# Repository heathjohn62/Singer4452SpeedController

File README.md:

# Singer4452-speed-controller

This project implements PID feedback to improve control over the Singer 4452 sewing machine. The modifications are non-destructive to the sewing machine. 

Implement this at your own risk. I do not have an electrical engineering degree nor am I a certified electrician. 120V AC flows through the sewing machine pedal and the PID regulator board, which can electrocute you, start fires, and break things. Don't perform work on circuits that are plugged into the wall. 

As an outline:
1. A rotary encoder tracks the position of the sewing needle by mounting externally to the knob on the side of the machine. The FreeCAD design for the rotary encoder is contained in "rotary-encoder-CAD". Some hardware, a magnet, rubber tape, duct tape, and a ball bearing are also required to assemble this. The PCB for the rotary encoder IC in contained in "speed-sensor-PCB."
2. A network of optoisolated resistors emulate the potentiometer in the existing pedal. Resistance is programmed by a MCU. The MCU and resistor network are enclosed in a chasis, and the design for the PCB is in the folder "Regulator-PCB." The STM32 was programmed in the STM32CubeIDE using the files in the folder "sewing-PID-STM32-program".
3. The circuit board in the original pedal is redesigned. The slide potentiometer provides input to the MCU instead of providing the timing to an RC oscillator as in the original pedal. The RC osillator is timed by the variable resistor network in the regulator PCB. The BT136-600E triac is exchanged for a higher current BT137-600E, and an additional 100 ohm and 0.1uF snubber is added to mitigate stress on the motor and triac. A fuse and varistor are added as short circuit and overvoltage protection. 

Errors and other notes:
- In my original rotary encoder design, pin 5 on the AS5600-ASOT was grounded. This was a mistake, and the pin should be left open. This is now fixed in KiCAD, but for my own sewing machine I just pried the IC pin off of the PCB. 
- The 5V barrel jack runs directly into the enclosure when positioned as it currently is on the PCB. I cut the barrel off and soldered the wires directly to the PCB. This is not currently fixed in the KiCAD design. 
- The AC mains connect to the foot pedal using 0.110" quick-connect tabs. I designed the board for two-prong 0.187" tabs (TE 1-726388-2), which don't fit the mains cables. I didn't want to pay for shipping again, so I bent one of the two prongs on the tabs so that one could be soldered into the PCB and the other into the mains cable. This is fine, but the better part to use would be something like TE 62395-1. 
- "foot-pedal-PCB" contains a folder "spice" with a (very approximate) simulation of the triac trigger circuit in the foot pedal. I used this to better understand the circuit in the original pedal and improve the design. In my hands, the triac model used by the simulation refuses to latch on PC, but works great on mac. 
- **This is likely not the best solution to this problem**. Using an optoisolated resistor network to adjust an RC timer takes up a ton of space and parts, and could be replaced by a circuit that exactly controls the phase angle modulation using only few optoisolators. I did not know I would be redesigning the foot pedal PCB after designing the regulator PCB. I'm now satisfied with the handling of my Singer 4452, so I have no plans to engineer this further. 
- Materials I ordered for this project can be found in the "orders" folder. Other things you would need include a soldering iron, hot air rework station or reflow oven, a drill, wire crimpers, STLink/V2 debugger and TAG-connect adapter, some metric machine screws and standoffs. I recommend anti-static precautions when working with STM32s.

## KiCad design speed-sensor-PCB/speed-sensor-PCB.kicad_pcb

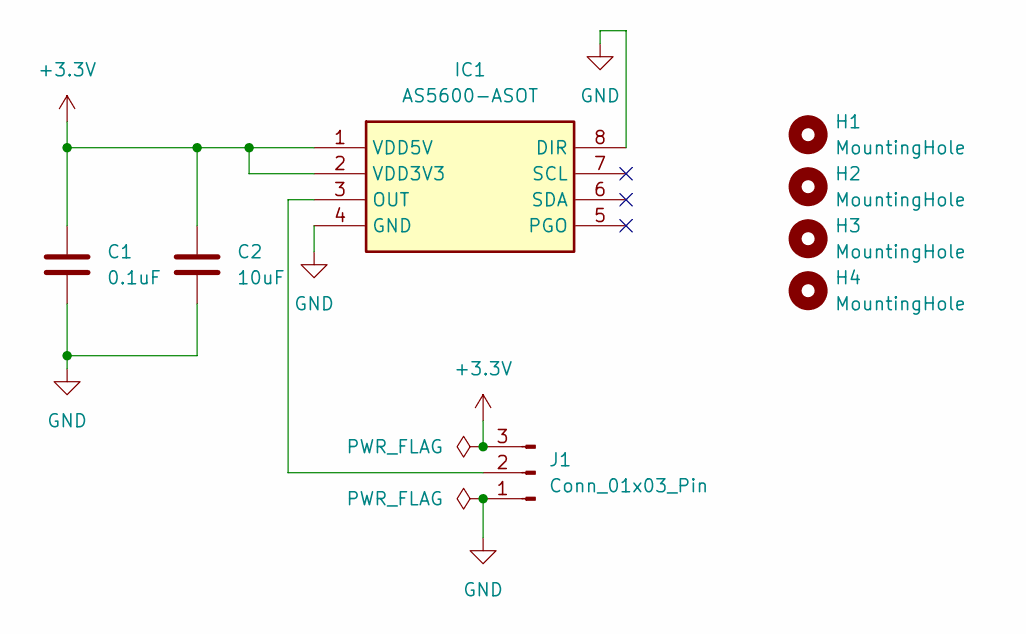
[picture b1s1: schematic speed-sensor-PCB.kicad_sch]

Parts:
C1: 0.1uF; CAP_C320_KEM; Part # C320C104K5R5TA
C2: 10uF; CP_Radial_Tantal_D5.5mm_P5.00mm; Part # FG20X7R1H106KRT06
H1, H2, H3, H4: MountingHole; MountingHole_3.2mm_M3_ISO7380
IC1: AS5600-ASOT; SOIC-8_3.9x4.9mm_P1.27mm; Mouser Part Number 985-AS5600-ASOT
J1: Conn_01x03_Pin; JST_VH_B3P-VH-FB-B_1x03_P3.96mm_Vertical

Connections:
+3.3V: C1.1, C2.1, IC1.1 (VDD5V), IC1.2 (VDD3V3), J1.3
GND: C1.2, C2.2, IC1.4 (GND), IC1.8 (DIR), J1.1
unnamed: IC1.3 (OUT), J1.2

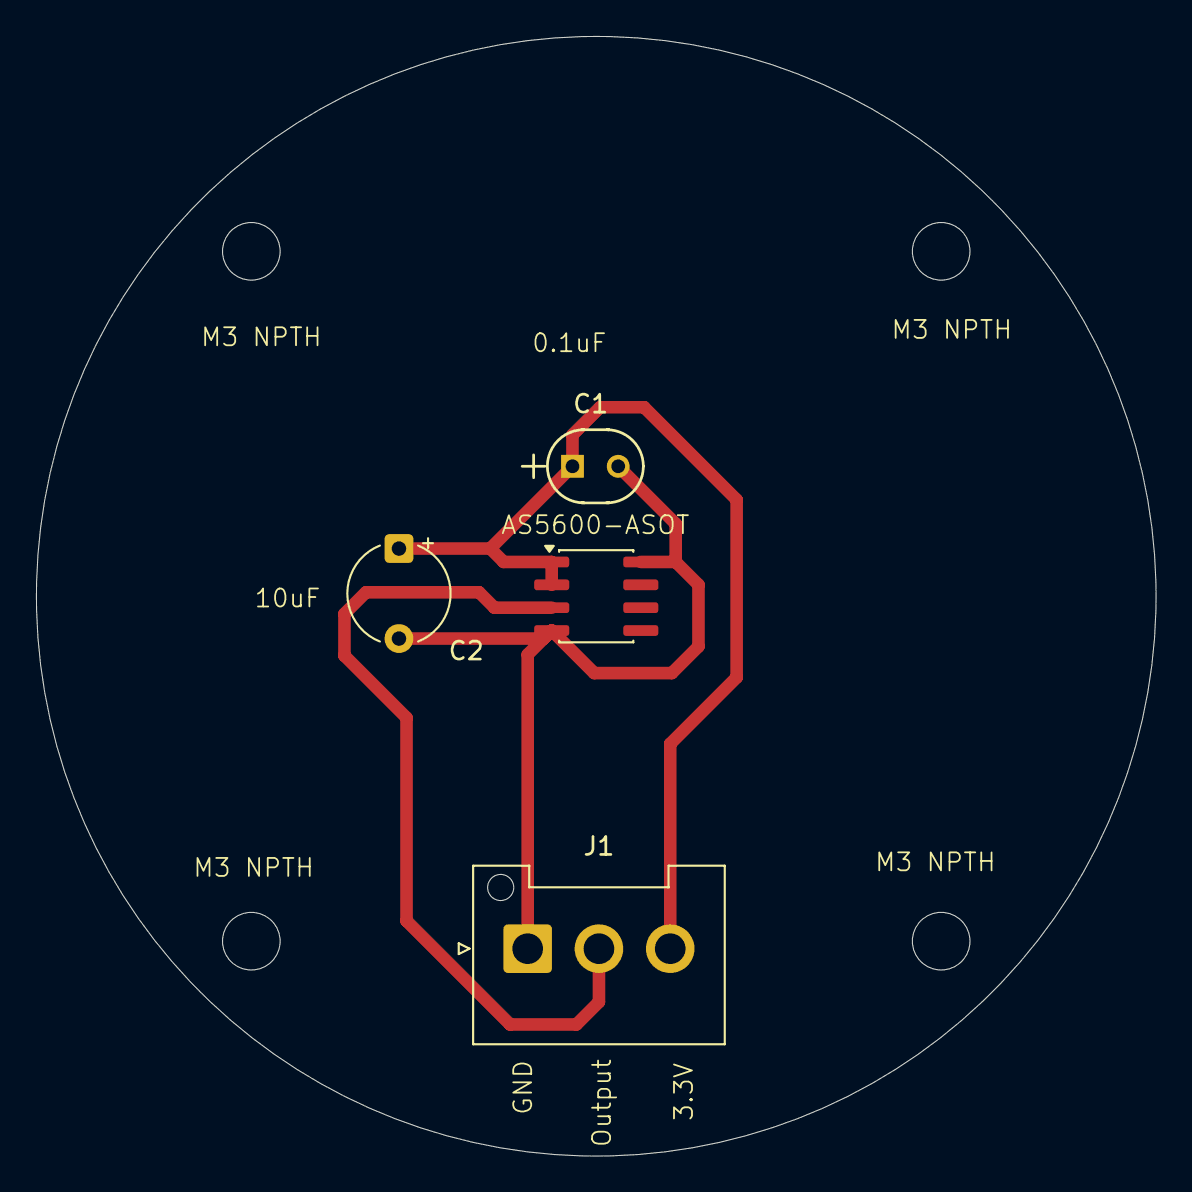
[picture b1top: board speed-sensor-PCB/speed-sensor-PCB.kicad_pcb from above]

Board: 2 copper layers, 62.2 x 62.2 mm, 8 parts (0 on the bottom side), 3 nets.

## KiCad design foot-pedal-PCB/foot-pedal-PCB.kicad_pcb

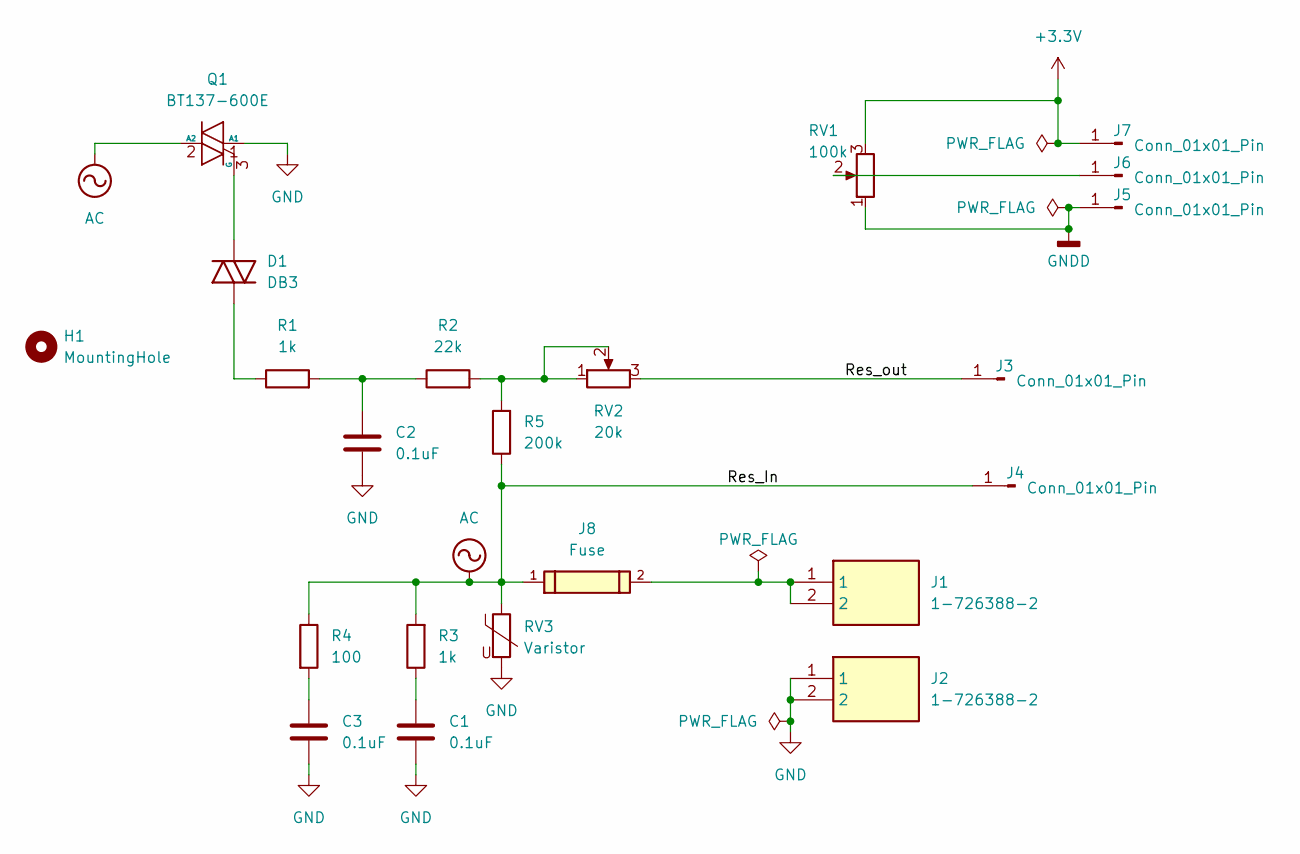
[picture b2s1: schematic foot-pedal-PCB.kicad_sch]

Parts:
C1, C2, C3: 0.1uF; C_Rect_L18.0mm_W5.0mm_P15.00mm_FKS3_FKP3; MFG # BFC233627104; Mouser # 594-222233627104
D1: DB3; D_DO-35_SOD27_P7.62mm_Horizontal; MFG # DB3; Mouser # 511-DB3
H1: MountingHole; MountingHole_5.5mm
J1, J2: 1-726388-2; 17263882; Mouser # 571-1-726388-2
J3, J4, J5, J6, J7: Conn_01x01_Pin; SolderWire-0.5sqmm_1x01_D0.9mm_OD2.1mm
J8: Fuse; 696108003002; MFG # 696108003002
Q1: BT137-600E; MFG # BT137-600E,127; Mouser # 771-BT137-600E
R1: 1k; R_Axial_DIN0516_L15.5mm_D5.0mm_P20.32mm_Horizontal; MFG # CPF31K0000FKE14; Mouser # 71-CPF31K0000FKE14
R2: 22k; R_Axial_DIN0207_L6.3mm_D2.5mm_P10.16mm_Horizontal; MFG # SFR25H0002202FA500; Mouser # 594-SFR25H0002202FA5
R3: 1k; R_Axial_DIN0207_L6.3mm_D2.5mm_P10.16mm_Horizontal; MFG # SFR25H0001001FA500; Mouser # 594-SFR25H0001001FA5
R4: 100; R_Axial_DIN0516_L15.5mm_D5.0mm_P20.32mm_Horizontal; MFG # CPF3100R00FKE14; Mouser # 71-CPF3100R00FKE14
R5: 200k; R_Axial_DIN0207_L6.3mm_D2.5mm_P10.16mm_Horizontal; MFG # PR01000102003FA500; Mouser # 594-PR01000102003FA5
RV1: 100k; RA2043F2010EB1B100K; MFG # RA2043F-20-10EB1-B100K; Mouser # 312-219BF-100K
RV2: 20k; POT_3329H; MFG # 3329H-1-203LF; Mouser # 652-3329H-1-203LF
RV3: Varistor; VAR_B72214P2301K101; MFG # B72214P2301K101

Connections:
+3.3V: J7.1, RV1.3
/Res_out: J3.1, RV2.3
AC: J4.1, J8.1, Q1.2 (A2), R3.2, R4.1, R5.1, RV3.1
GND: C1.1, C2.1, C3.1, J2.1, J2.2, Q1.1 (A1), RV3.2
GNDD: J5.1, RV1.1
unnamed: C1.2, R3.1
unnamed: C2.2, R1.2, R2.1
unnamed: C3.2, R4.2
unnamed: D1.2 (A), Q1.3 (G)
unnamed: D1.1 (K), R1.1
unnamed: J1.1, J1.2, J8.2
unnamed: J6.1, RV1.2
unnamed: R2.2, R5.2, RV2.1, RV2.2

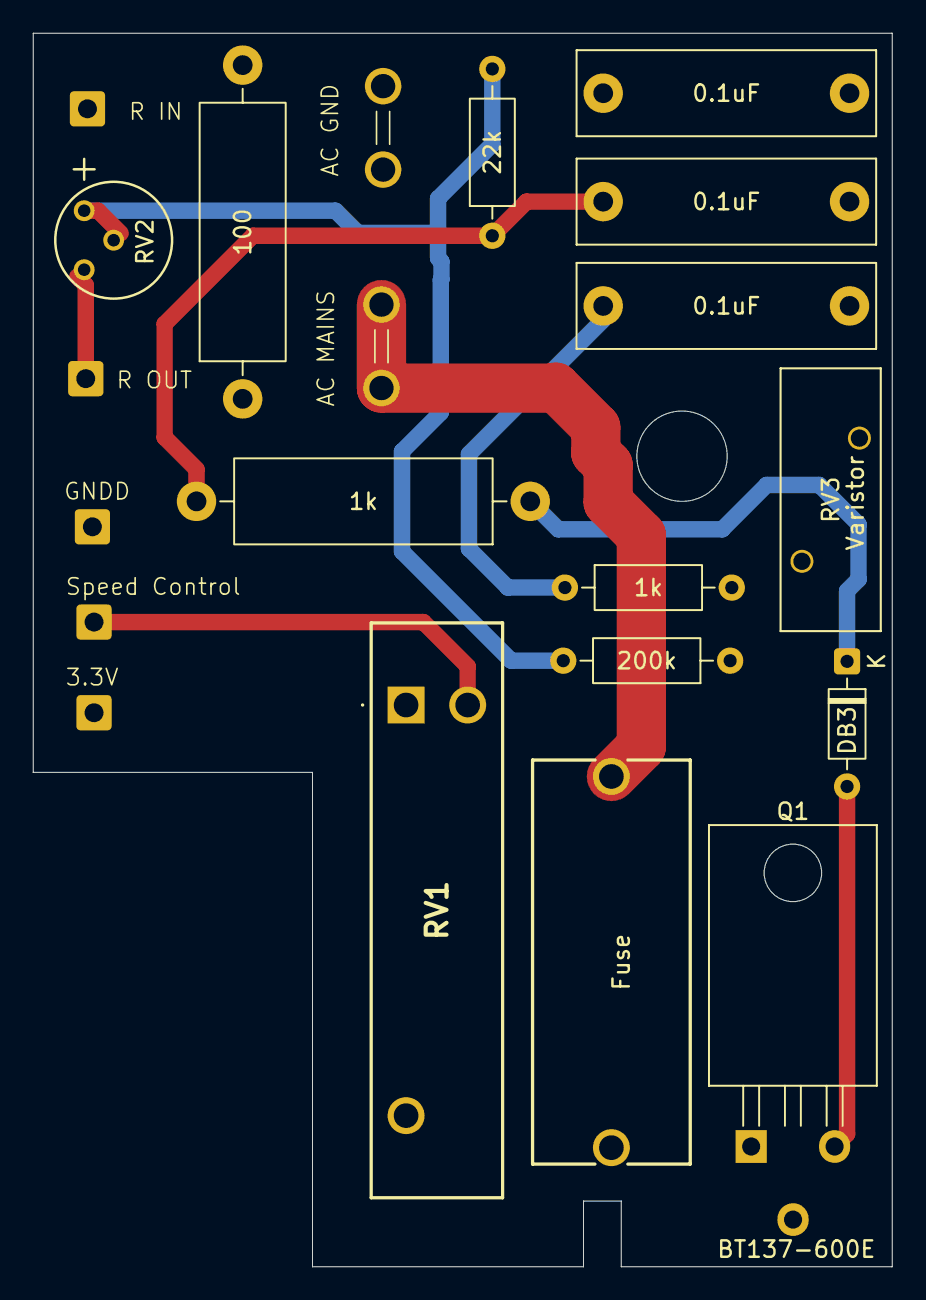
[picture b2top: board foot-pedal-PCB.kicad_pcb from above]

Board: 4 copper layers, 52.3 x 75.1 mm, 22 parts (0 on the bottom side), 13 nets.

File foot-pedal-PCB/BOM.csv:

Reference,Qty,OrderQnty,Value,MFG,Mouser #,Description
"C1,C2,C3",3,10,0.1uF,Vishay,594-222233627104,Safety Capacitors .1uF 10% 275volts
D1,1,2,DB3,,511-DB3,"32V 2A Bidirectional trigger diode, DO-35"
"J1,J2",2,10,1-726388-2,TE Connectivity,571-1-726388-2,"Tab terminal,PCB, FASTON 187, straight TE Connectivity FASTON .187 Series , Straight Mount Angle PCB Tab Terminal, 4.75 x 0.81mm Tin Plated"
Q1,1,2,BT137-600E,,771-BT137-600E ,Triacs RAIL TRIAC
R1,1,2,1k,Vishay,71-CPF31K0000FKE14,Metal Film Resistors - Through Hole 3watts 1Kohms 1% 100ppm
R2,1,2,22k,Vishay,594-SFR25H0002202FA5 ,Metal Film Resistors - Through Hole SFR25H 1% A5 22K
R3,1,2,1k,,594-SFR25H0001001FA5,Metal Film Resistors SFR25H 1% A5 1K0
R4,1,2,100,Vishay,71-CPF3100R00FKE14 ,Metal Film Resistors 3watts 100ohms 1% 100ppm
R5,1,2,200k,Vishay,594-PR01000102003FA5 ,Metal Film Resistors PR01 1% A5 200K
RV1,1,2,100k,Alpha (Taiwan),312-219BF-100K,Trimmer Resistors - Through Hole T7 YA 100K 20% BO e2
RV2,1,2,20k,Bourns,652-3329H-1-203LF,"Trimmer Resistors - Through Hole 1/4""RND 20KOHMS 10% 0.5WATTS"

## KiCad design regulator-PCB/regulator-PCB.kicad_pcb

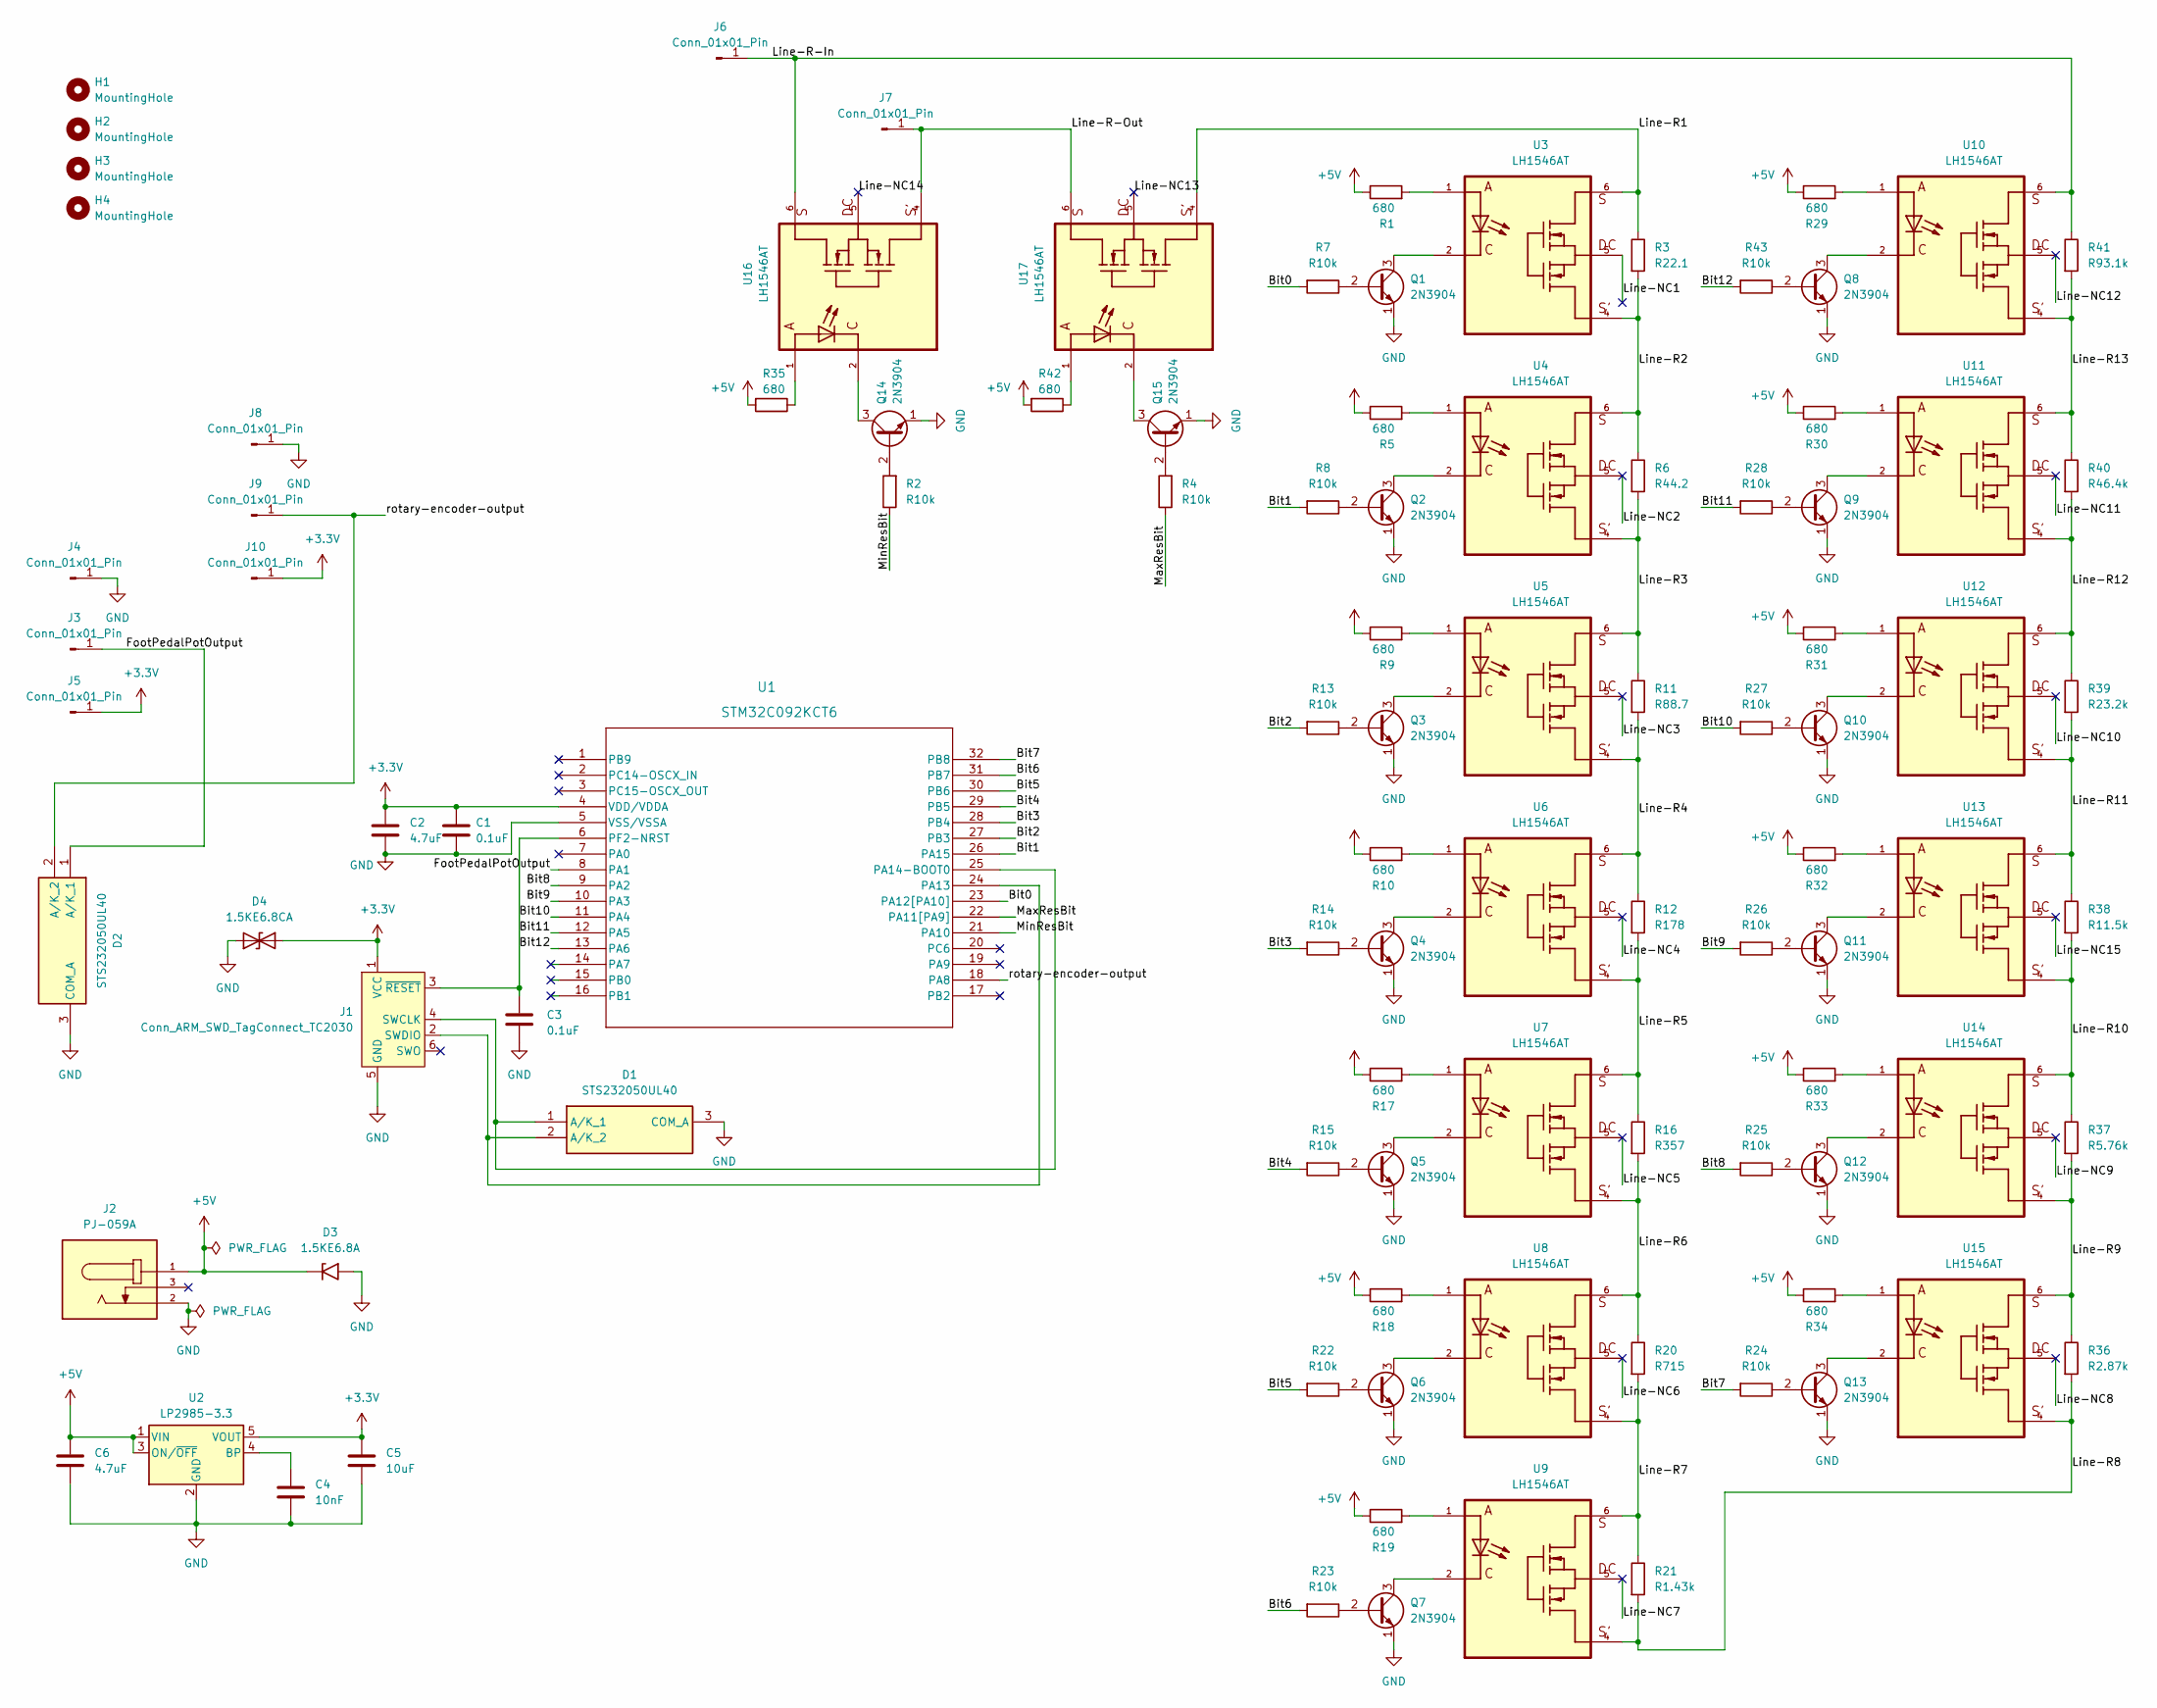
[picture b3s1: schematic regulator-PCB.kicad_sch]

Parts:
C1, C3: 0.1uF; CAP_C320_KEM; Part # C320C104K5R5TA
C2, C6: 4.7uF; CAPRB500W50L450T300H550; Part # FG24X7R1E475KRT00
C4: 10nF; C_Rect_L13.0mm_W4.0mm_P10.00mm_FKS3_FKP3_MKS4; Part # B32621A6103J189
C5: 10uF; CP_Radial_Tantal_D5.5mm_P5.00mm; Part # FG20X7R1H106KRT06
D1, D2: STS232050UL40; Mouser Part Number 504-STS232050UL40
D3: 1.5KE6.8A; D_DO-201AE_P15.24mm_Horizontal
D4: 1.5KE6.8CA; D_DO-201AE_P15.24mm_Horizontal
H1, H2, H3, H4: MountingHole; MountingHole_4.5mm
J1: Conn_ARM_SWD_TagConnect_TC2030; Tag-Connect_TC2030-IDC-FP_2x03_P1.27mm_Vertical
J2: PJ-059A; CUI_PJ-059A; PARTREV 1.04
J3, J4, J5, J6, J7, J8, J9, J10: Conn_01x01_Pin; SolderWire-0.75sqmm_1x01_D1.25mm_OD2.3mm_Relief
Q1, Q2, Q3, Q4, Q5, Q6, Q7, Q8, Q9, Q10, Q11, Q12, Q13, Q14, Q15: 2N3904; TO-92_Inline
R1, R5, R9, R10, R17, R18, R19, R29, R30, R31, R32, R33, R34, R35, R42: 680; R_Axial_DIN0207_L6.3mm_D2.5mm_P10.16mm_Horizontal; MFG # LR1F680R
R2, R4, R7, R8, R13, R14, R15, R22, R23, R24, R25, R26, R27, R28, R43: R10k; R_Axial_DIN0207_L6.3mm_D2.5mm_P10.16mm_Horizontal; MFG # MFR-25FRF52-10K
R3: R22.1; R_Axial_DIN0207_L6.3mm_D2.5mm_P10.16mm_Horizontal; MFG # RNF14FTD22R1
R6: R44.2; R_Axial_DIN0207_L6.3mm_D2.5mm_P10.16mm_Horizontal; MFG # MFR-25FRF52-44R2
R11: R88.7; R_Axial_DIN0207_L6.3mm_D2.5mm_P10.16mm_Horizontal; MFG # MFR-25FBF52-88R7
R12: R178; R_Axial_DIN0207_L6.3mm_D2.5mm_P10.16mm_Horizontal; MFG # MFR-25FBF52-178R
R16: R357; R_Axial_DIN0207_L6.3mm_D2.5mm_P10.16mm_Horizontal; MFG # MFR-25FBF52-357R
R20: R715; R_Axial_DIN0207_L6.3mm_D2.5mm_P10.16mm_Horizontal; MFG # MFR-25FBF52-715R
R21: R1.43k; R_Axial_DIN0207_L6.3mm_D2.5mm_P10.16mm_Horizontal; MFG # MFR-25FBF52-1K43
R36: R2.87k; R_Axial_DIN0207_L6.3mm_D2.5mm_P10.16mm_Horizontal; MFG # MFR-25FBF52-2K87
R37: R5.76k; R_Axial_DIN0207_L6.3mm_D2.5mm_P10.16mm_Horizontal; MFG # MFR-25FRF52-5K76
R38: R11.5k; R_Axial_DIN0207_L6.3mm_D2.5mm_P10.16mm_Horizontal; MFG # MFR-25FBF52-11K5
R39: R23.2k; R_Axial_DIN0207_L6.3mm_D2.5mm_P10.16mm_Horizontal; MFG # MFR-25FBF52-11K5
R40: R46.4k; R_Axial_DIN0207_L6.3mm_D2.5mm_P10.16mm_Horizontal; MFG # MFR-25FRF52-46K4
R41: R93.1k; R_Axial_DIN0207_L6.3mm_D2.5mm_P10.16mm_Horizontal; MFG # MFR-25FBF52-93K1
U1: STM32C092KCT6; LQFP-32_7x7mm_P0.8mm; Part # STM32C092KCT6
U2: LP2985-3.3; SOT-23-5
U3, U4, U5, U6, U7, U8, U9, U10, U11, U12, U13, U14, U15, U16, U17: LH1546AT; DIP762W50P254L730H410Q6

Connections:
+3.3V: C1.1, C2.1, C5.1, D4.2 (A2), J1.1 (VCC), J5.1, J10.1, U1.4 (VDD/VDDA), U2.5 (VOUT)
+5V: C6.1, D3.1 (A1), J2.1, R1.1, R5.1, R9.1, R10.1, R17.1, R18.1, R19.1, R29.1, R30.1, R31.1, R32.1, R33.1, R34.1, R35.2, R42.2, U2.1 (VIN), U2.3 (ON/~OFF)
/Bit0: R7.2, U1.23 (PA12[PA10])
/Bit1: R8.2, U1.26 (PA15)
/Bit2: R13.2, U1.27 (PB3)
/Bit3: R14.2, U1.28 (PB4)
/Bit4: R15.2, U1.29 (PB5)
/Bit5: R22.2, U1.30 (PB6)
/Bit6: R23.2, U1.31 (PB7)
/Bit7: R24.2, U1.32 (PB8)
/Bit8: R25.2, U1.9 (PA2)
/Bit9: R26.2, U1.10 (PA3)
/Bit10: R27.2, U1.11 (PA4)
/Bit11: R28.2, U1.12 (PA5)
/Bit12: R43.2, U1.13 (PA6)
/FootPedalPotOutput: D2.1 (A/K_1), J3.1, U1.8 (PA1)
/Line-NC1: U3.5
/Line-NC2: U4.5
/Line-NC3: U5.5
/Line-NC4: U6.5
/Line-NC5: U7.5
/Line-NC6: U8.5
/Line-NC7: U9.5
/Line-NC8: U15.5
/Line-NC9: U14.5
/Line-NC10: U12.5
/Line-NC11: U11.5
/Line-NC12: U10.5
/Line-NC13: U17.5
/Line-NC14: U16.5
/Line-NC15: U13.5
/Line-R1: R3.1, U3.6, U17.4
/Line-R2: R3.2, R6.1, U3.4, U4.6
/Line-R3: R6.2, R11.1, U4.4, U5.6
/Line-R4: R11.2, R12.1, U5.4, U6.6
/Line-R5: R12.2, R16.1, U6.4, U7.6
/Line-R6: R16.2, R20.1, U7.4, U8.6
/Line-R7: R20.2, R21.1, U8.4, U9.6
/Line-R8: R21.2, R36.2, U9.4, U15.4
/Line-R9: R36.1, R37.2, U14.4, U15.6
/Line-R10: R37.1, R38.2, U13.4, U14.6
/Line-R11: R38.1, R39.2, U12.4, U13.6
/Line-R12: R39.1, R40.2, U11.4, U12.6
/Line-R13: R40.1, R41.2, U10.4, U11.6
/Line-R-In: J6.1, R41.1, U10.6, U16.6
/Line-R-Out: J7.1, U16.4, U17.6
/MaxResBit: R4.1, U1.22 (PA11[PA9])
/MinResBit: R2.1, U1.21 (PA10)
/rotary-encoder-output: D2.2 (A/K_2), J9.1, U1.18 (PA8)
GND: C1.2, C2.2, C3.2, C4.2, C5.2, C6.2, D1.3 (COM_A), D2.3 (COM_A), D3.2 (A2), D4.1 (A1), J1.5 (GND), J2.2, J4.1, J8.1, Q1.1 (E), Q2.1 (E), Q3.1 (E), Q4.1 (E), Q5.1 (E), Q6.1 (E), Q7.1 (E), Q8.1 (E), Q9.1 (E), Q10.1 (E), Q11.1 (E), Q12.1 (E), Q13.1 (E), Q14.1 (E), Q15.1 (E), U1.5 (VSS/VSSA), U2.2 (GND)
unnamed: D1.1 (A/K_1), J1.4 (SWCLK), U1.25 (PA14-BOOT0)
unnamed: D1.2 (A/K_2), J1.2 (SWDIO), U1.24 (PA13)
unnamed: C3.1, J1.3 (~RESET), U1.6 (PF2-NRST)
unnamed: Q1.2 (B), R7.1
unnamed: Q1.3 (C), U3.2
unnamed: Q2.2 (B), R8.1
unnamed: Q2.3 (C), U4.2
unnamed: Q3.2 (B), R13.1
unnamed: Q3.3 (C), U5.2
unnamed: Q4.2 (B), R14.1
unnamed: Q4.3 (C), U6.2
unnamed: Q5.2 (B), R15.1
unnamed: Q5.3 (C), U7.2
unnamed: Q6.2 (B), R22.1
unnamed: Q6.3 (C), U8.2
unnamed: Q7.2 (B), R23.1
unnamed: Q7.3 (C), U9.2
unnamed: Q8.2 (B), R43.1
unnamed: Q8.3 (C), U10.2
unnamed: Q9.2 (B), R28.1
unnamed: Q9.3 (C), U11.2
unnamed: Q10.2 (B), R27.1
unnamed: Q10.3 (C), U12.2
unnamed: Q11.2 (B), R26.1
unnamed: Q11.3 (C), U13.2
unnamed: Q12.2 (B), R25.1
unnamed: Q12.3 (C), U14.2
unnamed: Q13.2 (B), R24.1
unnamed: Q13.3 (C), U15.2
unnamed: Q14.2 (B), R2.2
unnamed: Q14.3 (C), U16.2
unnamed: Q15.2 (B), R4.2
unnamed: Q15.3 (C), U17.2
unnamed: R1.2, U3.1
unnamed: R5.2, U4.1
unnamed: R9.2, U5.1
unnamed: R10.2, U6.1
unnamed: R17.2, U7.1
unnamed: R18.2, U8.1
unnamed: R19.2, U9.1
unnamed: R29.2, U10.1
unnamed: R30.2, U11.1
unnamed: R31.2, U12.1
unnamed: R32.2, U13.1
unnamed: R33.2, U14.1
unnamed: R34.2, U15.1
unnamed: R35.1, U16.1
unnamed: R42.1, U17.1
unnamed: C4.1, U2.4 (BP)

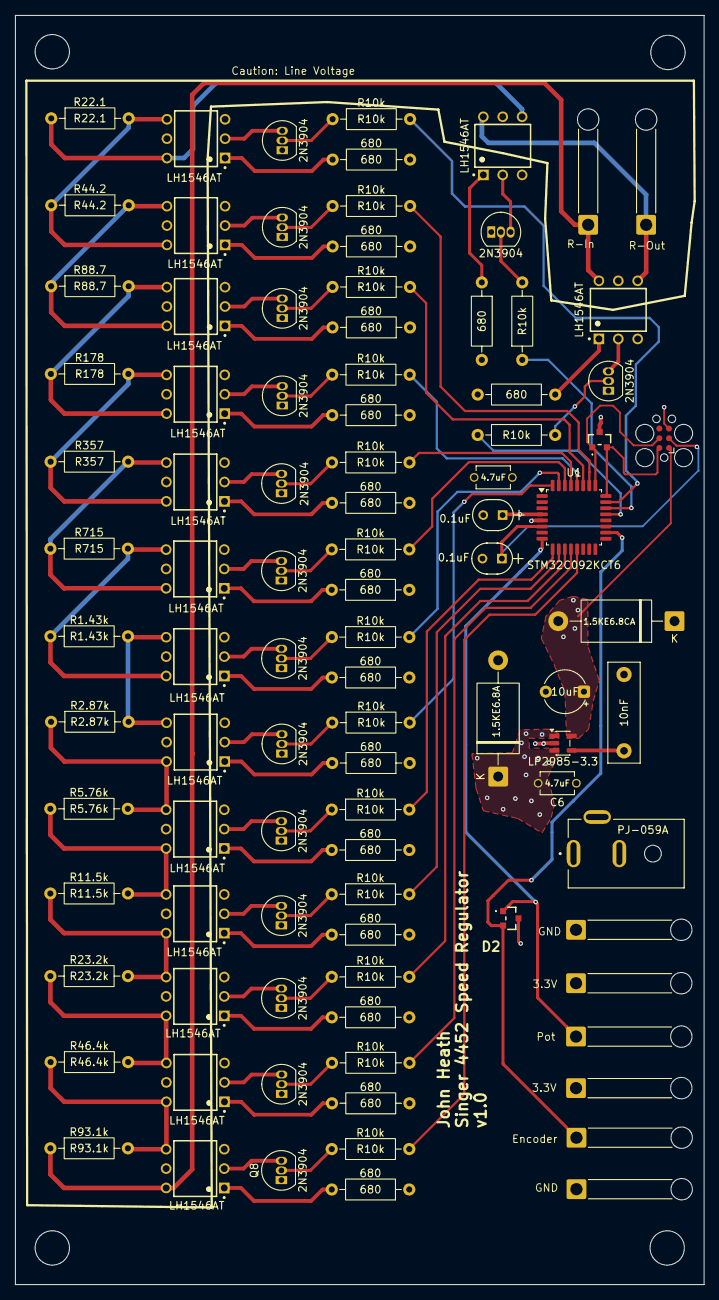
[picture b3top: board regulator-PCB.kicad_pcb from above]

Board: 4 copper layers, 90.3 x 166.4 mm, 99 parts (0 on the bottom side), 84 nets.

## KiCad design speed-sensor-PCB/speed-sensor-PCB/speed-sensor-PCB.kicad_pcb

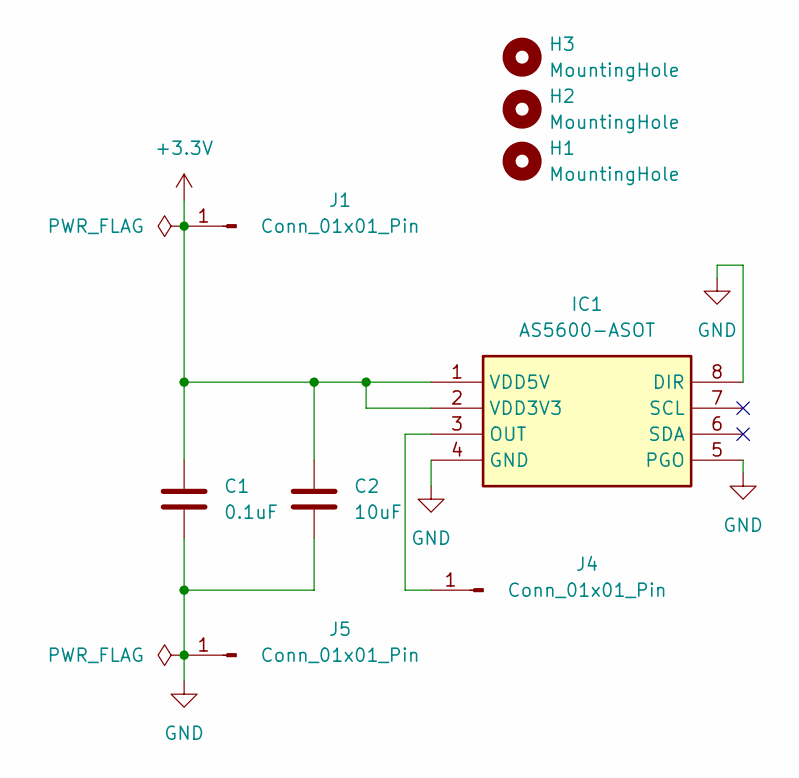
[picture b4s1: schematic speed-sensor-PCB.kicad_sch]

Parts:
C1: 0.1uF; C_Disc_D5.0mm_W2.5mm_P2.50mm; Part # C320C104K5R5TA
C2: 10uF; CP_Radial_Tantal_D5.5mm_P5.00mm; Part # FG20X7R1H106KRT06
H1, H2, H3: MountingHole; MountingHole_6.4mm_M6_ISO14580
IC1: AS5600-ASOT; SOIC-8_3.9x4.9mm_P1.27mm; Mouser Part Number 985-AS5600-ASOT
J1, J4, J5: Conn_01x01_Pin; SolderWire-0.5sqmm_1x01_D0.9mm_OD2.1mm_Relief

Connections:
+3.3V: C1.1, C2.1, IC1.1 (VDD5V), IC1.2 (VDD3V3), J1.1
GND: C1.2, C2.2, IC1.4 (GND), IC1.5 (PGO), IC1.8 (DIR), J5.1
unnamed: IC1.3 (OUT), J4.1

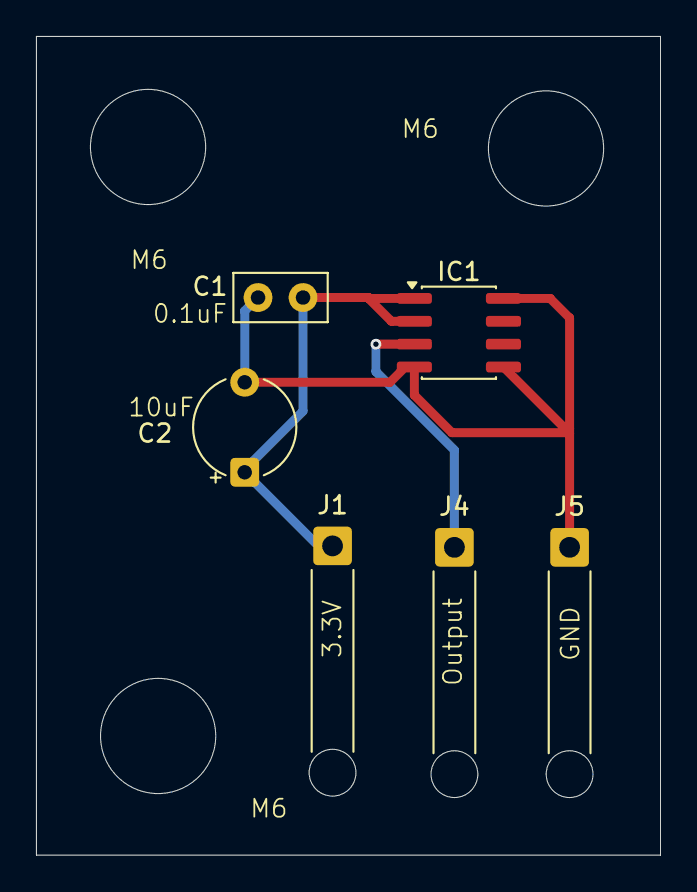
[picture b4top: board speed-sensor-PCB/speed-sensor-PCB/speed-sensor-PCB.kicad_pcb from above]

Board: 2 copper layers, 34.7 x 45.5 mm, 9 parts (0 on the bottom side), 3 nets.

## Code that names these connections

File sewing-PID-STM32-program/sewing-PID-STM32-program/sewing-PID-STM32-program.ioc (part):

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Mcu.Name=STM32C092KCTx
Mcu.Package=LQFP32
Mcu.UserName=STM32C092KCTx
PA1.Mode=IN1
PA1.Signal=ADC1_IN1
PA10.Signal=GPIO_Output
PA11\ [PA9].Signal=GPIO_Output
PA12\ [PA10].Signal=GPIO_Output
PA15.Signal=GPIO_Output
PA2.Signal=GPIO_Output
PA3.Signal=GPIO_Output
PA4.Signal=GPIO_Output
PA5.Signal=GPIO_Output
PA6.Signal=GPIO_Output
PA8.Mode=IN8
PA8.Signal=ADC1_IN8
PB3.Signal=GPIO_Output
PB4.Signal=GPIO_Output
PB5.Signal=GPIO_Output
PB6.Signal=GPIO_Output
PB7.Signal=GPIO_Output
PB8.Signal=GPIO_Output
RCC.HSE_VALUE=8000000
RCC.SYSCLKFreq_VALUE=12000000
board=custom

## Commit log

2026-01-26 gitignore and README
2026-01-26 gitignore edits for kicad
2026-01-26 added chamfer to stabilizer
2026-01-27 initial schematic for regulator PCB
2026-01-29 ordered JST VH and made speed sensor PCB design
2026-01-29 Regular PCB schematic completed. Drafted a poor design for the regulator PCB, then added line voltage safety constraints. Pending PCB redesign.
2026-01-29 Regulator PCB v1.0 designed and ordered.
2026-01-29 cleaning up ordering
2026-01-29 removing stupid jupyter notebook
2026-01-31 worked out schematic for foot pedal PCB via reverse engineering and LTSpice
2026-02-01 fleshed out SPICE, finished pedal schematic v1.0, ordered pedal BOM from mouser.
2026-02-02 Added circuit protection, finished foot pedal PCB design, ordered from OSHPark
2026-02-06 working on program, fixed PGO connection on speed detector PCB
2026-02-06 implementing PID
2026-02-12 inverted pot
2026-02-12 README update
2026-02-16 adjusting control curve
2026-02-16 increased pot threshold to prevent motor bursts without pedal input
2026-02-18 added photo, cleaning up spice
